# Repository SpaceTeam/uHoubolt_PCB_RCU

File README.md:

# uHoubolt Radio Communication Unit (RCU) Hardware
## Known Issues
- Silkscreen Label of CAN1 and CAN2 are swapped

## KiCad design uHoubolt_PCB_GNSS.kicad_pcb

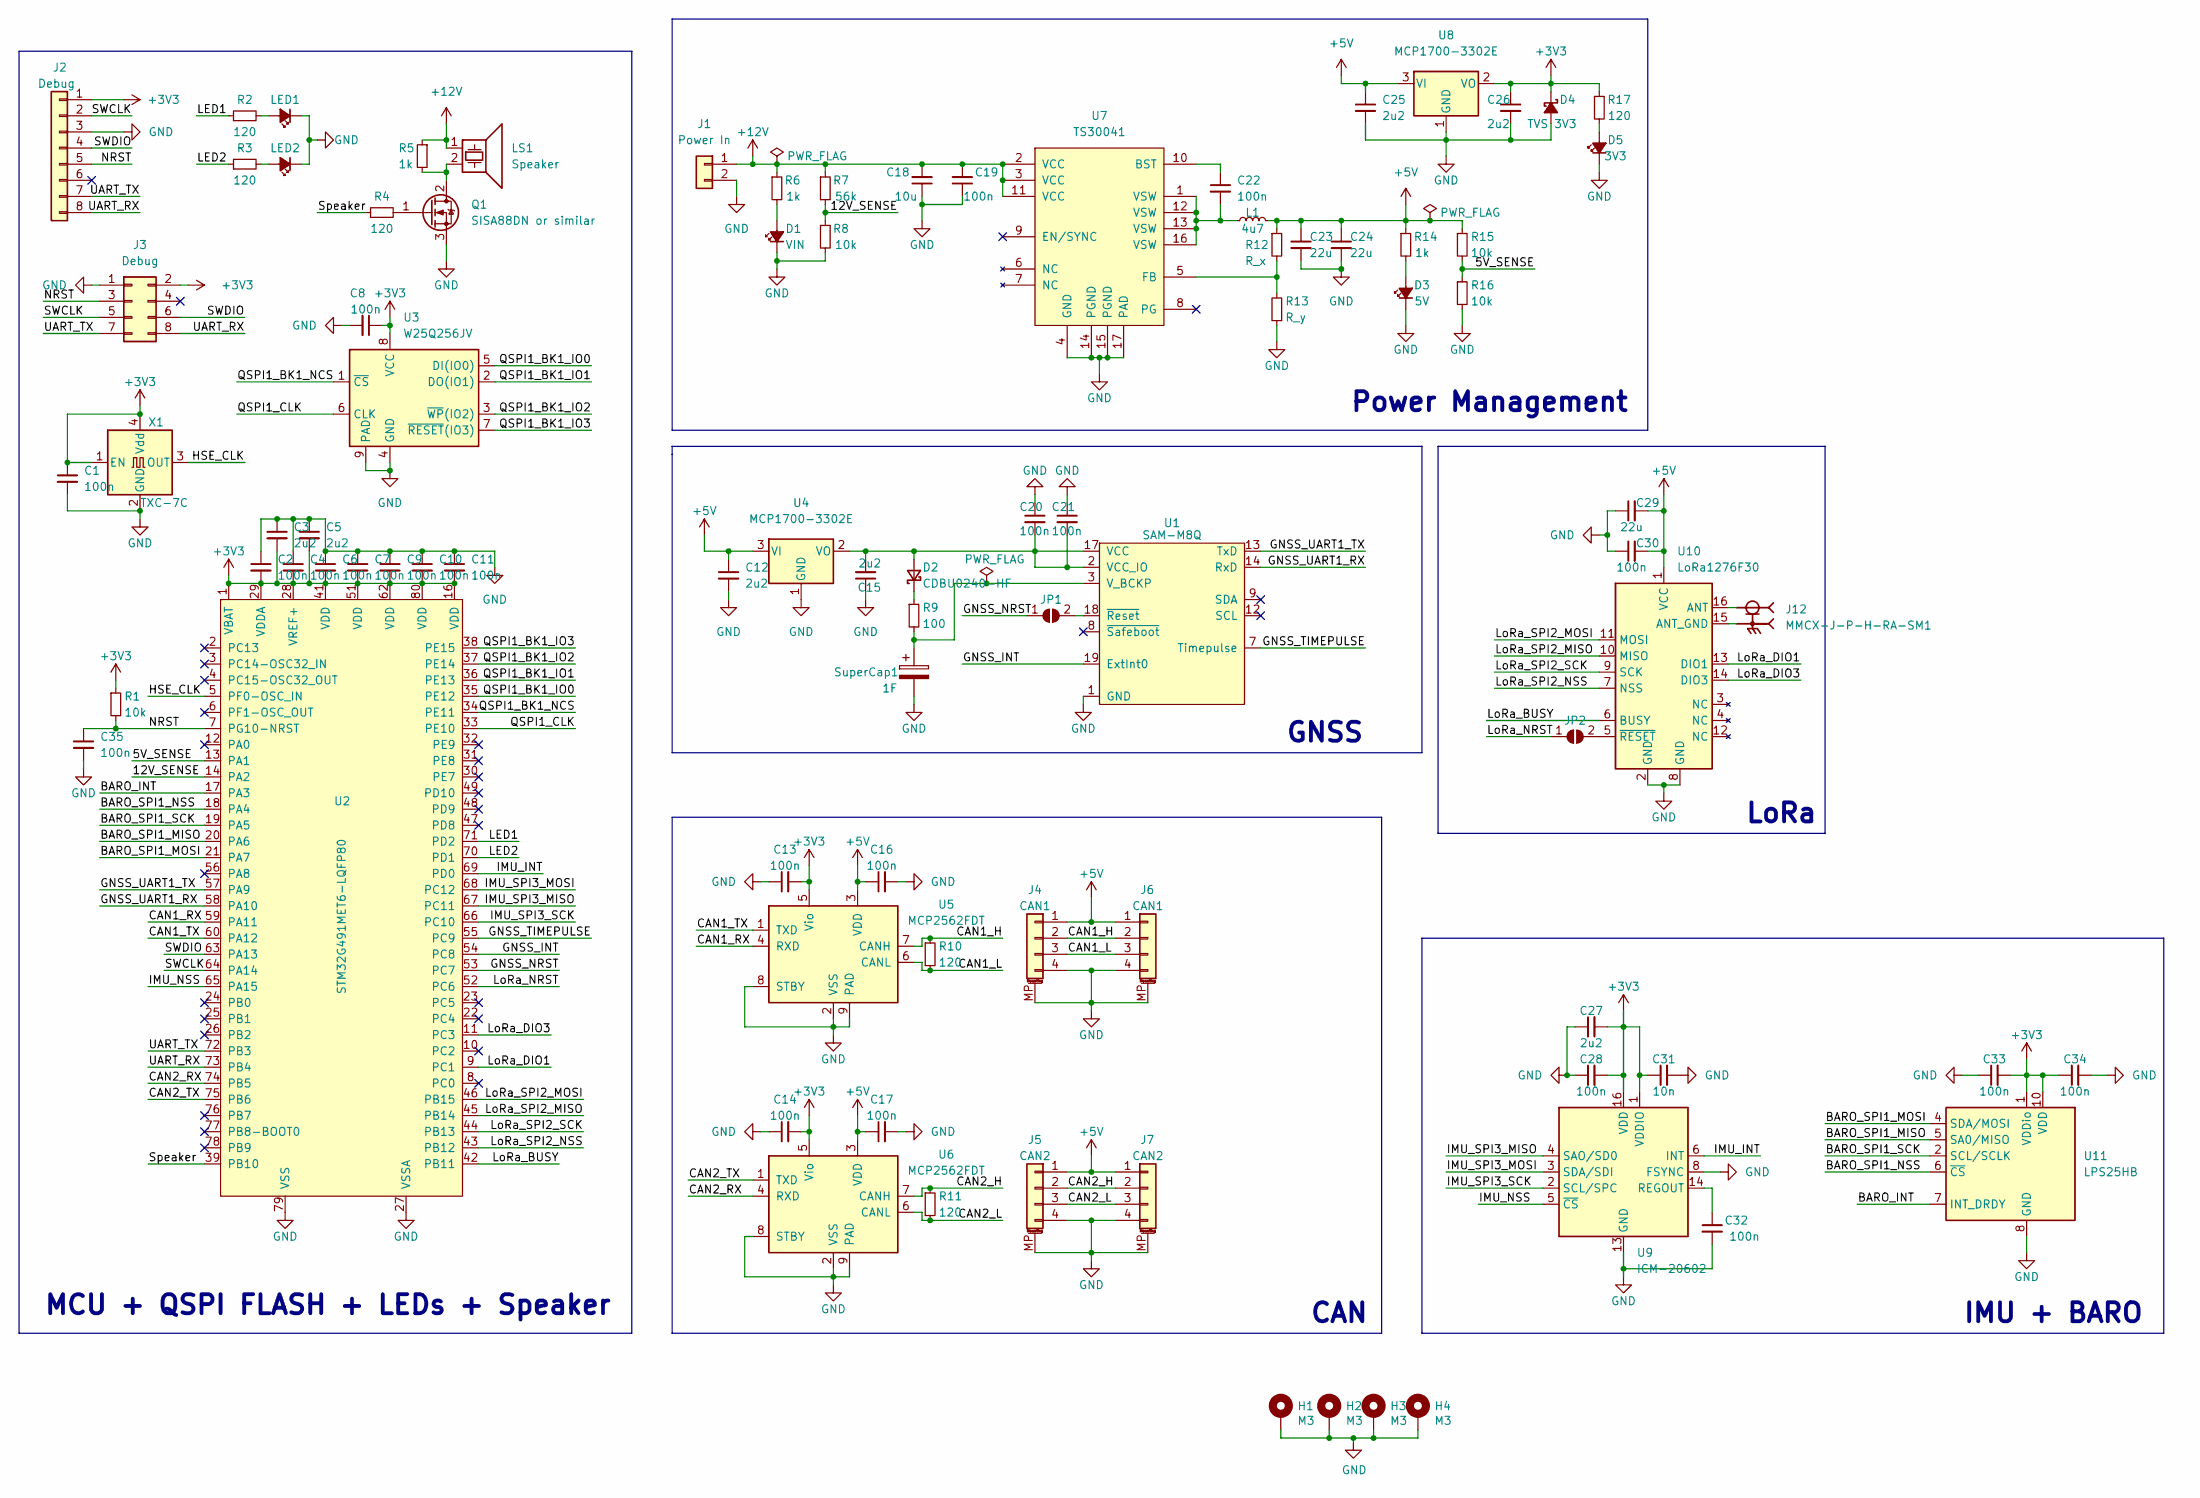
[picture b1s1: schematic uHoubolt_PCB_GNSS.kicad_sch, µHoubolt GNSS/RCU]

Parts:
C1, C2, C4, C6, C7, C8, C9, C10, C11, C13, C14, C16, C17, C19, C20, C21, C22, C28, C30, C32, C33, C34, C35: 100n; C_0603_1608Metric
C3, C5, C12, C15, C25, C26, C27: 2u2; C_0603_1608Metric
C18: 10u; C_0805_2012Metric
C23, C24, C29: 22u; C_0805_2012Metric
C31: 10n; C_0603_1608Metric
D1: VIN; LED_0603_1608Metric
D2: CDBU0240-HF; D_SOD-323F
D3: 5V; LED_0603_1608Metric
D4: TVS 3V3; SOD882D
D5: 3V3; LED_0603_1608Metric
H1, H2, H3, H4: M3; MountingHole_3.2mm_M3_Pad_Via
J1: Power In; Molex_Nano-Fit_105309-xx02_1x02_P2.50mm_Vertical
J2: Debug; PinHeader_1x08_P2.54mm_Vertical_SMD_Pin1Left
J3: Debug; PinHeader_2x04_P1.27mm_Vertical_SMD
J4, J6: CAN1; JST_GH_BM04B-GHS-TBT_1x04-1MP_P1.25mm_Vertical
J5, J7: CAN2; JST_GH_BM04B-GHS-TBT_1x04-1MP_P1.25mm_Vertical
J12: MMCX-J-P-H-RA-SM1; MMCX_Horizontal_THT; PARTREV F
JP1, JP2: SolderJumper_; SolderJumper-2_P1.3mm_Open_Pad1.0x1.5mm
L1: 4u7; SRN4018TA-4R7M
LED1, LED2: LED_Small_Filled; LED_0603_1608Metric
LS1: Speaker; Piezo_Buzzer
Q1: SISA88DN or similar; PowerPAK_1212-8
R1, R8, R15, R16: 10k; R_0603_1608Metric
R2, R3, R4, R10, R11, R17: 120; R_0603_1608Metric
R5, R6, R14: 1k; R_0603_1608Metric
R7: 56k; R_0603_1608Metric
R9: 100; R_0603_1608Metric
R12: R_x; R_0603_1608Metric
R13: R_y; R_0603_1608Metric
SuperCap1: 1F; CP_Elec_10x10.5
U1: SAM-M8Q
U2: STM32G491MET6-LQFP80; LQFP-80_12x12mm_P0.5mm
U3: W25Q256JV; WSON-8-8x6mm
U4, U8: MCP1700-3302E; SOT-23
U5, U6: MCP2562FDT; DFN-8-1EP_3x3mm_P0.65mm_EP1.55x2.4mm
U7: TS30041; QFN-16-1EP_3x3mm_P0.5mm_EP1.75x1.75mm_ThermalVias
U9: ICM-20602; LGA-16_3x3mm_P0.5mm_LayoutBorder3x5y
U10: LoRa1276F30; G-NiceRF-LoRa1268F30
U11: LPS25HB; ST_HLGA-10_2.5x2.5mm_P0.6mm_LayoutBorder3x2y
X1: TXC-7C; Oscillator_SMD_TXC_7C-4Pin_5.0x3.2mm

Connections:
+3V3: C1.1, C2.2, C3.2, C4.2, C5.2, C6.2, C7.2, C8.1, C9.2, C10.2, C11.2, C13.2, C14.2, C26.1, C27.2, C28.2, C31.1, C33.2, C34.1, D4.1 (K), J2.1, J3.2, R1.1, R17.1, U2.1 (VBAT), U2.16 (VDD), U2.28 (VREF+), U2.29 (VDDA), U2.41 (VDD), U2.51 (VDD), U2.62 (VDD), U2.80 (VDD), U3.8 (VCC), U5.5 (Vio), U6.5 (Vio), U8.2 (VO), U9.1 (VDDIO), U9.16 (VDD), U11.1 (VDDio), U11.10 (VDD), X1.1 (EN), X1.4 (Vdd)
+5V: C12.1, C16.1, C17.1, C23.1, C24.1, C25.1, C29.2, C30.2, J4.1, J5.1, J6.1, J7.1, L1.2, R12.1, R14.1, R15.1, U4.3 (VI), U5.3 (VDD), U6.3 (VDD), U8.3 (VI), U10.1 (VCC)
+12V: C18.2, C19.2, J1.1, LS1.1, R5.1, R6.1, R7.1, U7.2 (VCC), U7.3 (VCC), U7.11 (VCC)
/5V_SENSE: R15.2, R16.1, U2.13 (PA1)
/12V_SENSE: R7.2, R8.1, U2.14 (PA2)
/BARO_INT: U2.17 (PA3), U11.7 (INT_DRDY)
/BARO_SPI1_MISO: U2.20 (PA6), U11.5 (SA0/MISO)
/BARO_SPI1_MOSI: U2.21 (PA7), U11.4 (SDA/MOSI)
/BARO_SPI1_NSS: U2.18 (PA4), U11.6 (~CS)
/BARO_SPI1_SCK: U2.19 (PA5), U11.2 (SCL/SCLK)
/CAN1_H: J4.2, J6.2, R10.1, U5.7 (CANH)
/CAN1_L: J4.3, J6.3, R10.2, U5.6 (CANL)
/CAN1_RX: U2.59 (PA11), U5.4 (RXD)
/CAN1_TX: U2.60 (PA12), U5.1 (TXD)
/CAN2_H: J5.2, J7.2, R11.1, U6.7 (CANH)
/CAN2_L: J5.3, J7.3, R11.2, U6.6 (CANL)
/CAN2_RX: U2.74 (PB5), U6.4 (RXD)
/CAN2_TX: U2.75 (PB6), U6.1 (TXD)
/GNSS_INT: U1.19 (ExtInt0), U2.54 (PC8)
/GNSS_NRST: JP1.1 (A), U2.53 (PC7)
/GNSS_TIMEPULSE: U1.7 (Timepulse), U2.55 (PC9)
/GNSS_UART1_RX: U1.14 (RxD), U2.58 (PA10)
/GNSS_UART1_TX: U1.13 (TxD), U2.57 (PA9)
/HSE_CLK: U2.5 (PF0-OSC_IN), X1.3 (OUT)
/IMU_INT: U2.69 (PD0), U9.6 (INT)
/IMU_NSS: U2.65 (PA15), U9.5 (~CS)
/IMU_SPI3_MISO: U2.67 (PC11), U9.4 (SAO/SD0)
/IMU_SPI3_MOSI: U2.68 (PC12), U9.3 (SDA/SDI)
/IMU_SPI3_SCK: U2.66 (PC10), U9.2 (SCL/SPC)
/LED1: R2.1, U2.71 (PD2)
/LED2: R3.1, U2.70 (PD1)
/LoRa_BUSY: U2.42 (PB11), U10.6 (BUSY)
/LoRa_DIO1: U2.9 (PC1), U10.13 (DIO1)
/LoRa_DIO3: U2.11 (PC3), U10.14 (DIO3)
/LoRa_NRST: JP2.1 (A), U2.52 (PC6)
/LoRa_SPI2_MISO: U2.45 (PB14), U10.10 (MISO)
/LoRa_SPI2_MOSI: U2.46 (PB15), U10.11 (MOSI)
/LoRa_SPI2_NSS: U2.43 (PB12), U10.7 (NSS)
/LoRa_SPI2_SCK: U2.44 (PB13), U10.9 (SCK)
/NRST: C35.1, J2.5, J3.3, R1.2, U2.7 (PG10-NRST)
/QSPI1_BK1_IO0: U2.35 (PE12), U3.5 (DI(IO0))
/QSPI1_BK1_IO1: U2.36 (PE13), U3.2 (DO(IO1))
/QSPI1_BK1_IO2: U2.37 (PE14), U3.3 (~WP(IO2))
/QSPI1_BK1_IO3: U2.38 (PE15), U3.7 (~RESET(IO3))
/QSPI1_BK1_NCS: U2.34 (PE11), U3.1 (~CS)
/QSPI1_CLK: U2.33 (PE10), U3.6 (CLK)
/SWCLK: J2.2, J3.5, U2.64 (PA14)
/SWDIO: J2.4, J3.6, U2.63 (PA13)
/Speaker: R4.1, U2.39 (PB10)
/UART_RX: J2.8, J3.8, U2.73 (PB4)
/UART_TX: J2.7, J3.7, U2.72 (PB3)
GND: C1.2, C2.1, C3.1, C4.1, C5.1, C6.1, C7.1, C8.2, C9.1, C10.1, C11.1, C12.2, C13.1, C14.1, C15.1, C16.2, C17.2, C18.1, C19.1, C20.1, C21.1, C23.2, C24.2, C25.2, C26.2, C27.1, C28.1, C29.1, C30.1, C31.2, C32.2, C33.1, C34.2, C35.2, D1.1 (K), D3.1 (K), D4.2 (A), D5.1 (K), H1.1, H2.1, H3.1, H4.1, J1.2, J2.3, J3.1, J4.4, J4.MP (MountPin), J5.4, J5.MP (MountPin), J6.4, J6.MP (MountPin), J7.4, J7.MP (MountPin), LED1.1 (K), LED2.1 (K), Q1.3 (S), R8.2, R13.1, R16.2, SuperCap1.2, U1.1 (GND), U1.4 (GND), U1.5 (GND), U1.6 (GND), U1.10 (GND), U1.11 (GND), U1.15 (GND), U1.16 (GND), U1.20 (GND), U2.15 (VSS), U2.27 (VSSA), U2.40 (VSS), U2.50 (VSS), U2.61 (VSS), U2.79 (VSS), U3.4 (GND), U3.9 (PAD), U4.1 (GND), U5.2 (VSS), U5.8 (STBY), U5.9 (PAD), U6.2 (VSS), U6.8 (STBY), U6.9 (PAD), U7.4 (GND), U7.14 (PGND), U7.15 (PGND), U7.17 (PAD), U8.1 (GND), U9.8 (FSYNC), U9.9 (GND), U9.10 (GND), U9.11 (GND), U9.12 (GND), U9.13 (GND), U9.15 (GND), U10.2 (GND), U10.8 (GND), U11.3 (GND), U11.8 (GND), U11.9 (GND), X1.2 (GND)
unnamed: C15.2, C20.2, C21.2, D2.2 (A), U1.2 (VCC_IO), U1.17 (VCC), U4.2 (VO)
unnamed: C22.1, U7.10 (BST)
unnamed: C22.2, L1.1, U7.1 (VSW), U7.12 (VSW), U7.13 (VSW), U7.16 (VSW)
unnamed: C32.1, U9.14 (REGOUT)
unnamed: D1.2 (A), R6.2
unnamed: D2.1 (K), R9.1
unnamed: D3.2 (A), R14.2
unnamed: D5.2 (A), R17.2
unnamed: J12.1, U10.16 (ANT)
unnamed: J12.S1, J12.S2, J12.S3, J12.S4, U10.15 (ANT_GND)
unnamed: JP1.2 (B), U1.18 (~Reset)
unnamed: JP2.2 (B), U10.5 (~RESET)
unnamed: LED1.2 (A), R2.2
unnamed: LED2.2 (A), R3.2
unnamed: LS1.2, Q1.2 (D), R5.2
unnamed: Q1.1 (G), R4.2
unnamed: R9.2, SuperCap1.1, U1.3 (V_BCKP)
unnamed: R12.2, R13.2, U7.5 (FB)

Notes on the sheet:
CAN
MCU + QSPI FLASH + LEDs + Speaker
LoRa
GNSS
Power Management
IMU + BARO

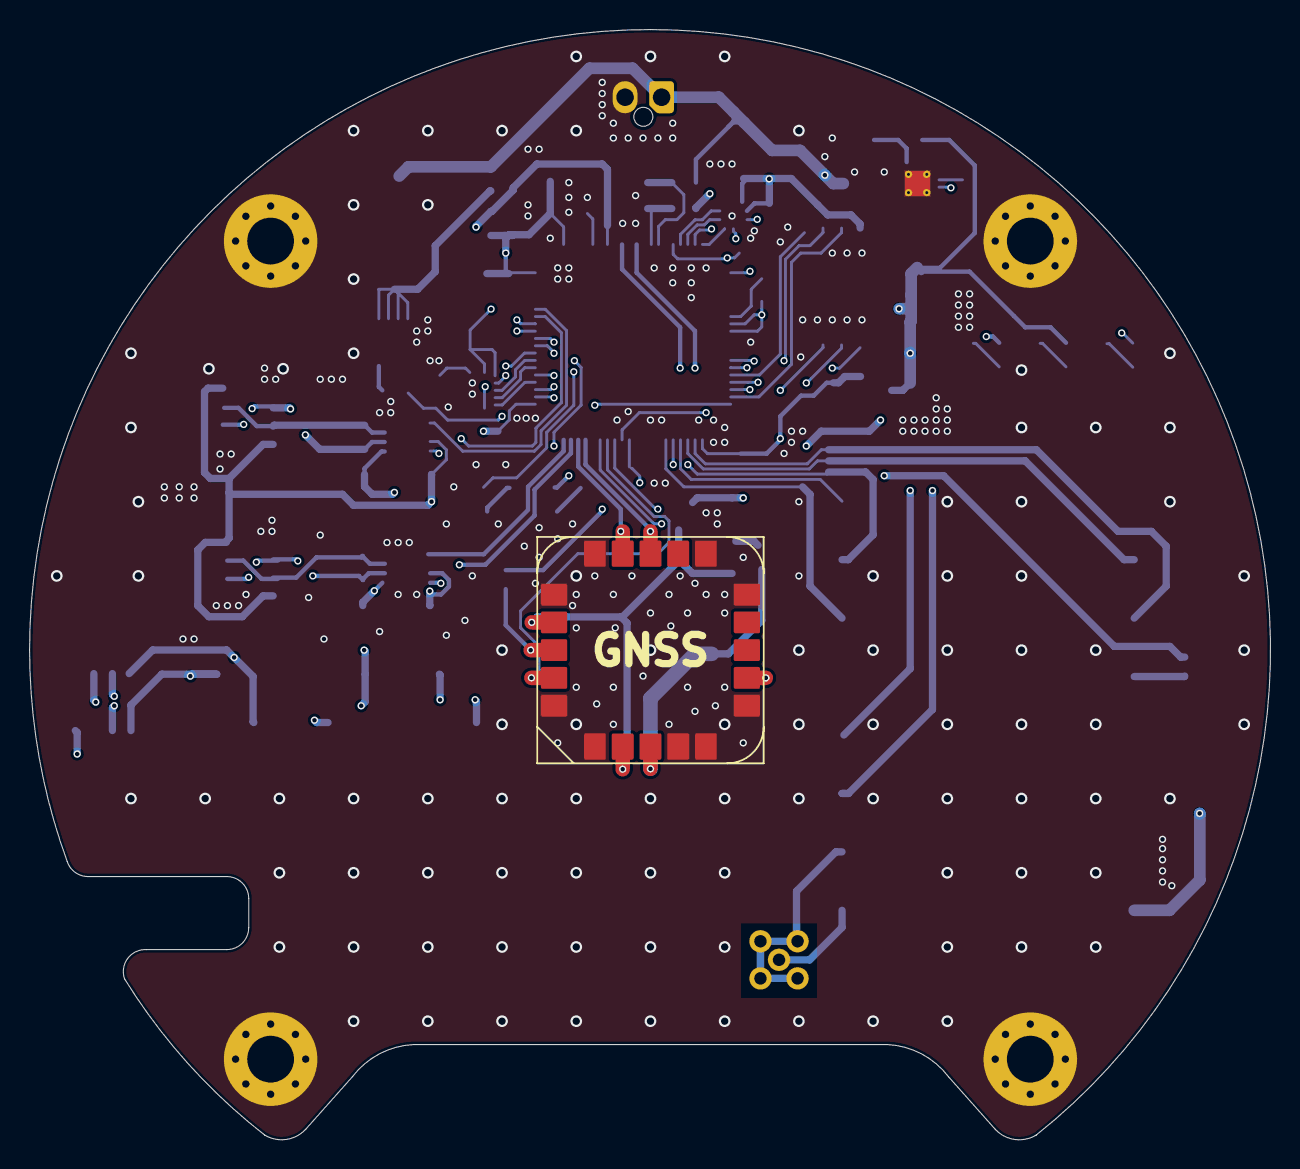
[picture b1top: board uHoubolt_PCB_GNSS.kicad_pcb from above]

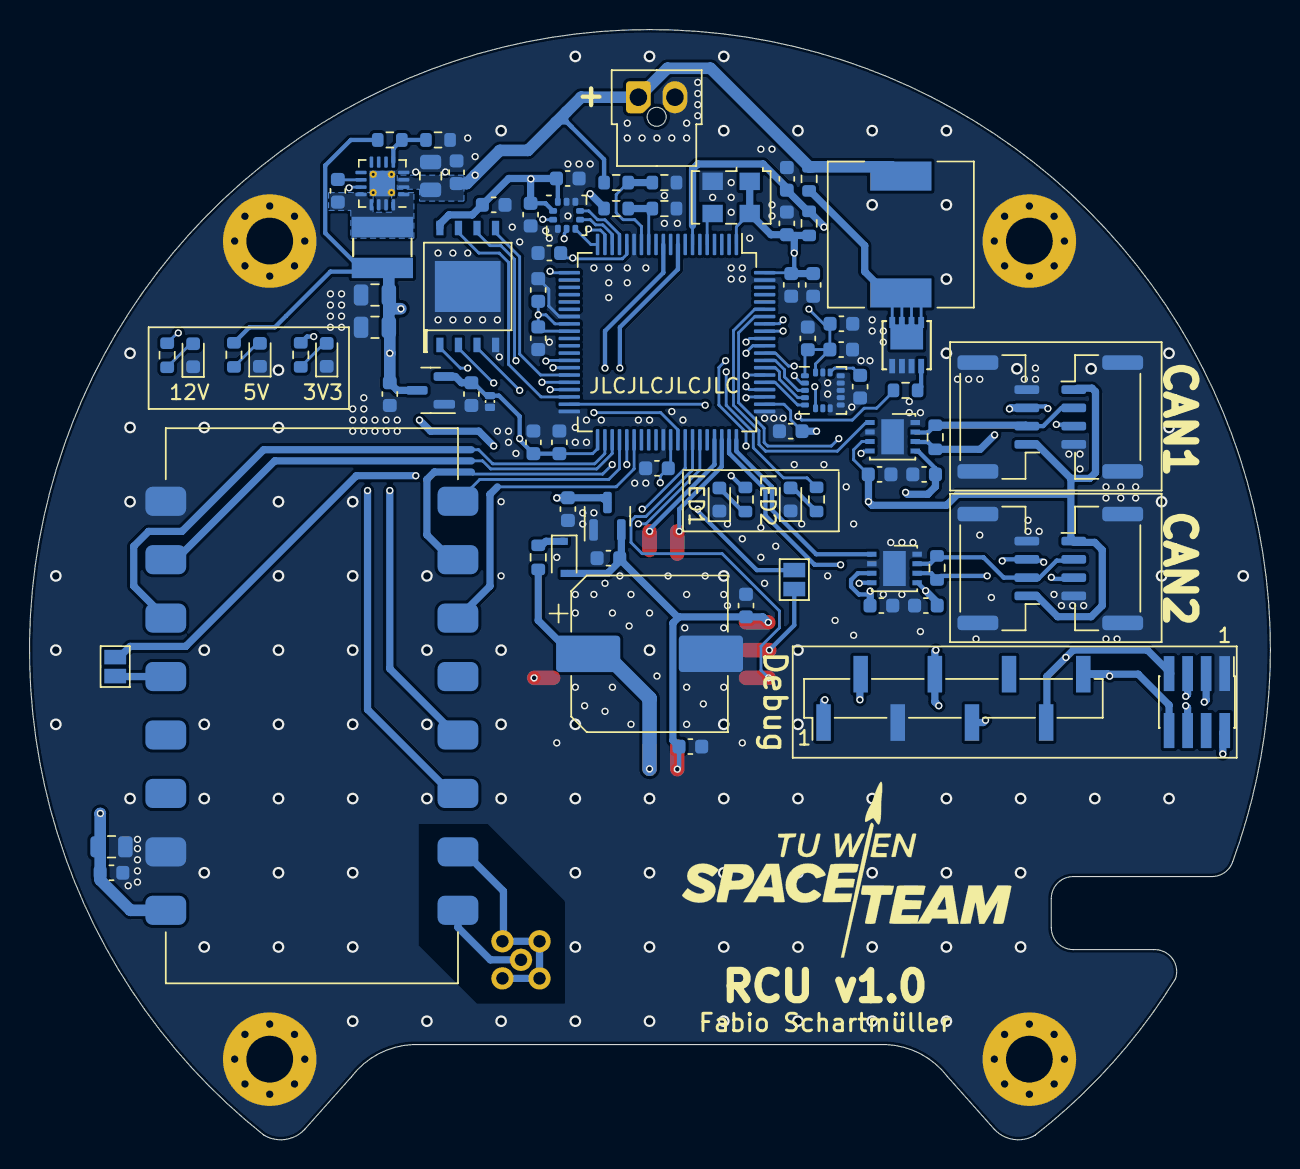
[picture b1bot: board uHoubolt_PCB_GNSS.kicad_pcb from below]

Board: 4 copper layers, 84.9 x 76.0 mm, 89 parts (84 on the bottom side), 70 nets.

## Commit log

2021-05-22 basic schematic and layout done, still missing: via stitching, mounting holes, backup cap, labels
2021-06-08 first revision done
2022-04-04 Update GNSS/RCU schematic. Add necessary components
2022-04-04 Fix LoRa DIO missconnection to STM32
2022-04-04 Fix false LDO for GNSS --> +3V3
2022-04-07 Add ignoration for annoying KiCad backups
2022-04-07 Update footprints and fixed minor naming fails.
2022-04-11 Updated layout; global placement done
2022-04-11 Updated submodule
2022-04-11 Update layout further
2022-04-12 Finished 1st proper layout
2022-04-12 Update (in)official board name INRCU -> IMRCU
2022-04-13 Update CAN transceiver footprints; removed redundant CAN jacks; replaced Power In Conn
2022-04-14 Fixed BARO INT and updated footprints for big caps
2022-04-18 Rounded board; updated LoRa module; Small bugfixes and rewiring
2022-05-08 Changed MMCX Footprint, Moved mounting holes, moved prog connectors
2022-05-08 Developed Balun for LoRa 433MHz loop antenna
2022-05-11 Cover
2022-05-12 RCU Release
2023-01-22 Add license
